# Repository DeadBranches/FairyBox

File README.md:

# FairyBox

### Software
A fork of [LilyTiny TinyTwinkle](https://github.com/deadbranch-forks/LilyTiny_LilyTwinkle)

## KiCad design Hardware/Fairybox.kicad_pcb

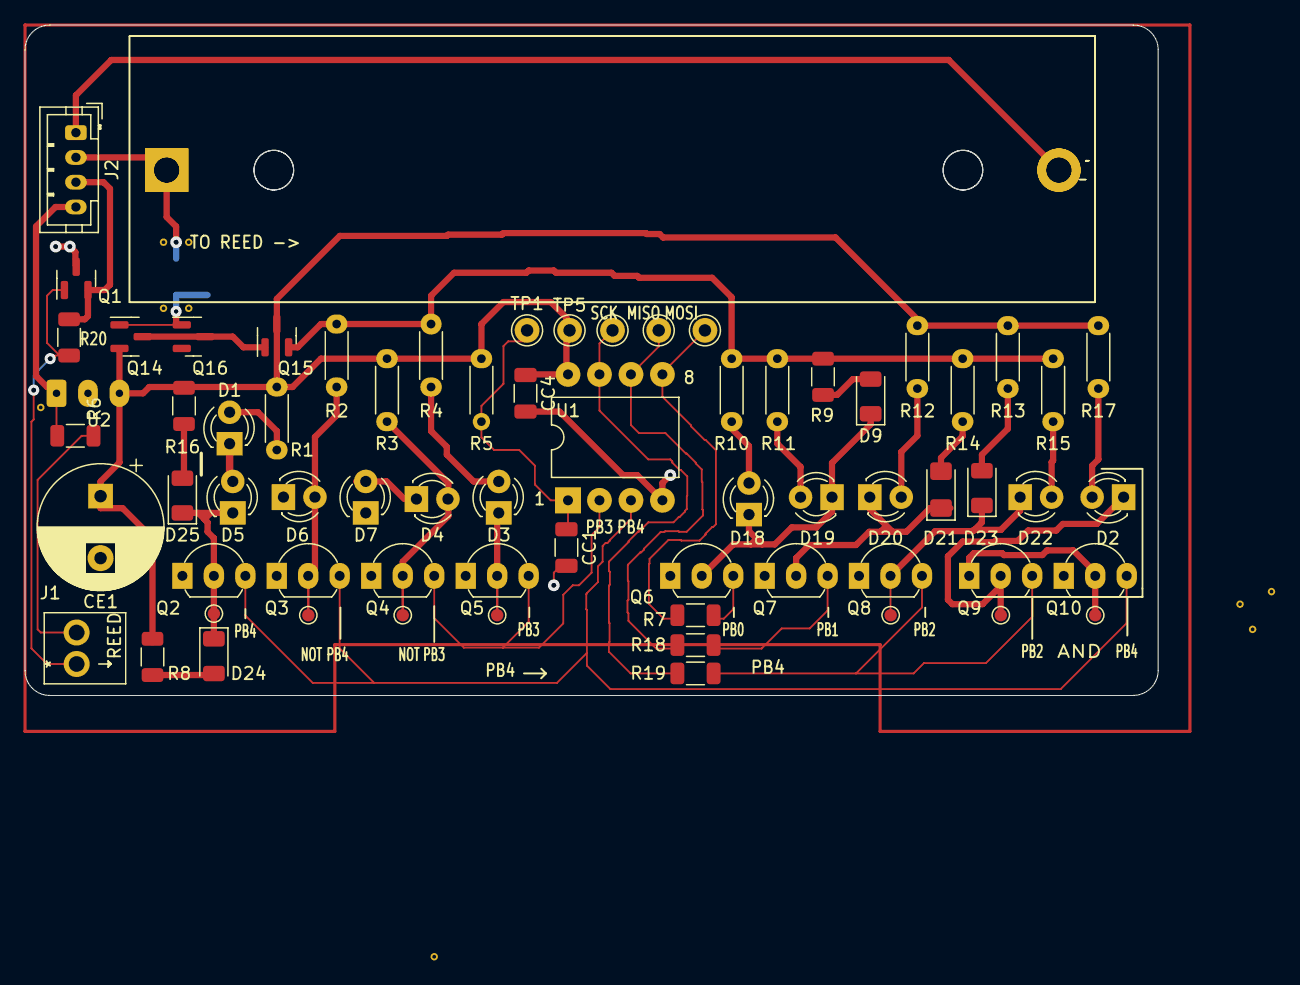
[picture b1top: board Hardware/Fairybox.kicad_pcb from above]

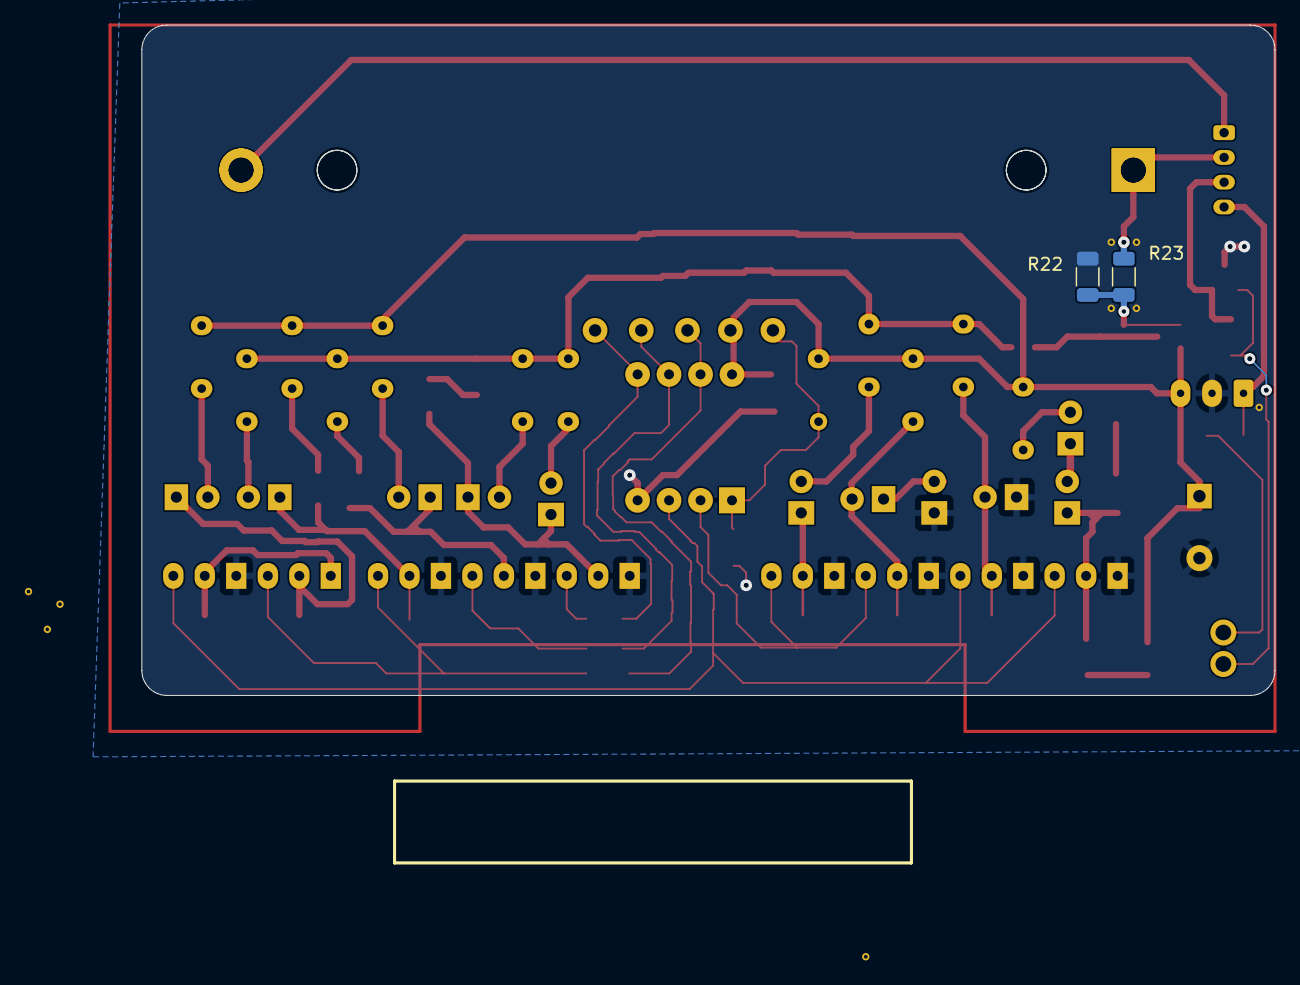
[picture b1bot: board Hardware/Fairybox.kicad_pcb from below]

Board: 2 copper layers, 91.4 x 54.1 mm, 81 parts (2 on the bottom side), 43 nets.

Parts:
BAT1, BAT1#2: locked; 18650 battery sled 1x
CC1: 0.22uF; C_1206_3216Metric
CC4: locked; C_1206_3216Metric
CE1: locked; CP_Radial_D10.0mm_P5.00mm
D1, D2, D3, D5, D6, D7, D18, D19, D20, D22: locked; LED_D3.0mm-DRC-larger-silk-footprint
D4: RED; LED_D3.0mm-DRC-larger-silk-footprint
D9, D24: BLUE; D_1206_3216Metric
D21: BLUE; D_1206_3216Metric_Pad1.42x1.75mm_HandSolder
D23, D25: RED; D_1206_3216Metric
J1: REED; KF128-2P
J2: JST B4B-PH-K-S; JST_PH_B4B-PH-K_1x04_P2.00mm_Vertical
JP1, JP3, JP5, JP9: ViaGND; Via-GND
JP2, JP4, JP6, JP7, JP8: ViaGND; PTH-Test_Point
Q1: locked; SOT-23
Q2, Q3, Q4, Q5, Q6, Q7, Q8, Q9, Q10: locked; TO-92L_Inline_Wide
Q14: AO3401A; SOT-23
Q15, Q16: SI2302; SOT-23
R1, R2, R3, R4, R5, R10, R11, R12, R13, R14, R15, R17: locked; R_Axial_DIN0204_L3.6mm_D1.6mm_P5.08mm_Horizontal
R6: 10K; R_1206_3216Metric
R7, R8, R18, R19: 470R; R_1206_3216Metric
R9: ??R; R_1206_3216Metric
R16: locked; R_1206_3216Metric
R20: 100K; R_1206_3216Metric
R22: 1M; R_1206_3216Metric
R23: 330k; R_1206_3216Metric
TP1: RST; Pin_D1.0mm_L10.0mm
TP2: locked; Pin_D1.0mm_L10.0mm
TP3: MISO; Pin_D1.0mm_L10.0mm
TP4: MOSI; Pin_D1.0mm_L10.0mm
TP5: VCC; Pin_D1.0mm_L10.0mm
TP6: TPP; TestPoint_Pad_D1.0mm
TP7: Q3_COL TP; TestPoint_Pad_D1.0mm
TP8: Q2_TP; TestPoint_Pad_D1.0mm
TP9: Q5_COL TP; TestPoint_Pad_D1.0mm
TP10: Q8_COL_TP; TestPoint_Pad_D1.0mm
TP11: Q9_COL_TP; TestPoint_Pad_D1.0mm
TP12: Q10_COL_TP; TestPoint_Pad_D1.0mm
U1: ATTINY85; DIP-8_W10.16mm
U2: locked; 3p-P2.54mm-big-pad-wire-holes

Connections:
+5V: CC4.1, CE1.1, Q14.2 (S), Q15.3 (D), R1.1, R3.1, R5.2, R8.1, R12.1, R13.1, R16.1, R17.1, TP5.1, U1.8 (VCC), U2.3 (VOUT)
/+5V B-LED: Q15.2 (S), R2.1, R4.1, R9.1, R10.1, R11.1, R14.1, R15.1
/CHARGE BOARD OUT B+: J2.4, R6.2, U2.1 (VIN)
/CHARGE BOARD OUT B-: J2.3, Q1.2 (S), R20.1
/D1_AN: D1.2 (A), R1.2
/D2_AN: D2.2 (A), R17.2
/D3_AN: D3.2 (A), R4.2
/D5_AN: D1.1 (K), D5.2 (A)
/D6_AN: D6.2 (A), Q3.2 (C), R2.2, TP7.1
/D7_AN: D4.1 (K), D7.2 (A)
/D9_AN: D9.2 (A), R9.2
/D18_AN: D18.2 (A), R10.2
/D19_AN: D19.2 (A), R11.2
/D20_AN: D20.2 (A), R12.2
/D21_AN: D22.2 (A), R15.2
/D22_AN: D21.2 (A), R14.2
/D23_AN: D23.2 (A), R13.2
/D24_AN: D24.2 (A), R8.2
/D25_AN: D25.2 (A), R16.2
/LBAT_NOT: Q14.1 (G), Q16.1 (G), R22.1, R23.2
/LI-ION_NEG: BAT1.2 (-), BAT1#2.2 (-), J2.2
/LI-ION_POS: BAT1.1 (+), BAT1#2.1 (+), J2.1, R22.2
/MCU GPIO0 MOSI: Q6.3 (B), R7.2
/MCU GPIO1 MISO: Q7.3 (B), R18.2
/MCU GPIO2 SCK: Q8.3 (B), Q9.3 (B), R19.2
/MCU GPIO3: Q4.3 (B), Q5.3 (B), U1.2 (PB3)
/MCU GPIO4: Q2.3 (B), Q3.3 (B), Q10.3 (B), U1.3 (PB4)
/MCU RST: CC1.1, R5.1, TP1.1, U1.1 (RST)
/PB0 PHY: R7.1, TP4.1, U1.5 (PB0)
/PB1 PHY: R18.1, TP3.1, U1.6 (PB1)
/PB2 PHY: R19.1, TP2.1, U1.7 (PB2)
/Q1_GATE: J1.2, Q1.1 (G), R20.2
/Q2_COL: D5.1 (K), D24.1 (K), D25.1 (K), Q2.2 (C), TP8.1
/Q4_COL: D4.2 (A), Q4.2 (C), R3.2, TP6.1
/Q5_COL: D3.1 (K), Q5.2 (C), TP9.1
/Q6_COL: D9.1 (K), D18.1 (K), D19.1 (K), Q6.2 (C)
/Q7_COL: D20.1 (K), D21.1 (K), Q7.2 (C)
/Q8_COL: D22.1 (K), D23.1 (K), Q8.2 (C), TP10.1
/Q9_COL: D2.1 (K), Q9.2 (C), TP11.1
/Q10_COL: Q9.1 (E), Q10.2 (C), TP12.1
/Q15_COL: Q14.3 (D), Q15.1 (G), Q16.3 (D)
/REED_IN: J1.1, R6.1
GND: CC1.2, CC4.2, CE1.2, D6.1 (K), D7.1 (K), JP1.1 (GND), JP2.1 (GND), JP3.1 (GND), JP4.1 (GND), JP5.1 (GND), JP6.1 (GND), JP7.1 (GND), JP8.1 (GND), JP9.1 (GND), Q1.3 (D), Q2.1 (E), Q3.1 (E), Q4.1 (E), Q5.1 (E), Q6.1 (E), Q7.1 (E), Q8.1 (E), Q10.1 (E), Q16.2 (S), R23.1, U2.2 (GND)

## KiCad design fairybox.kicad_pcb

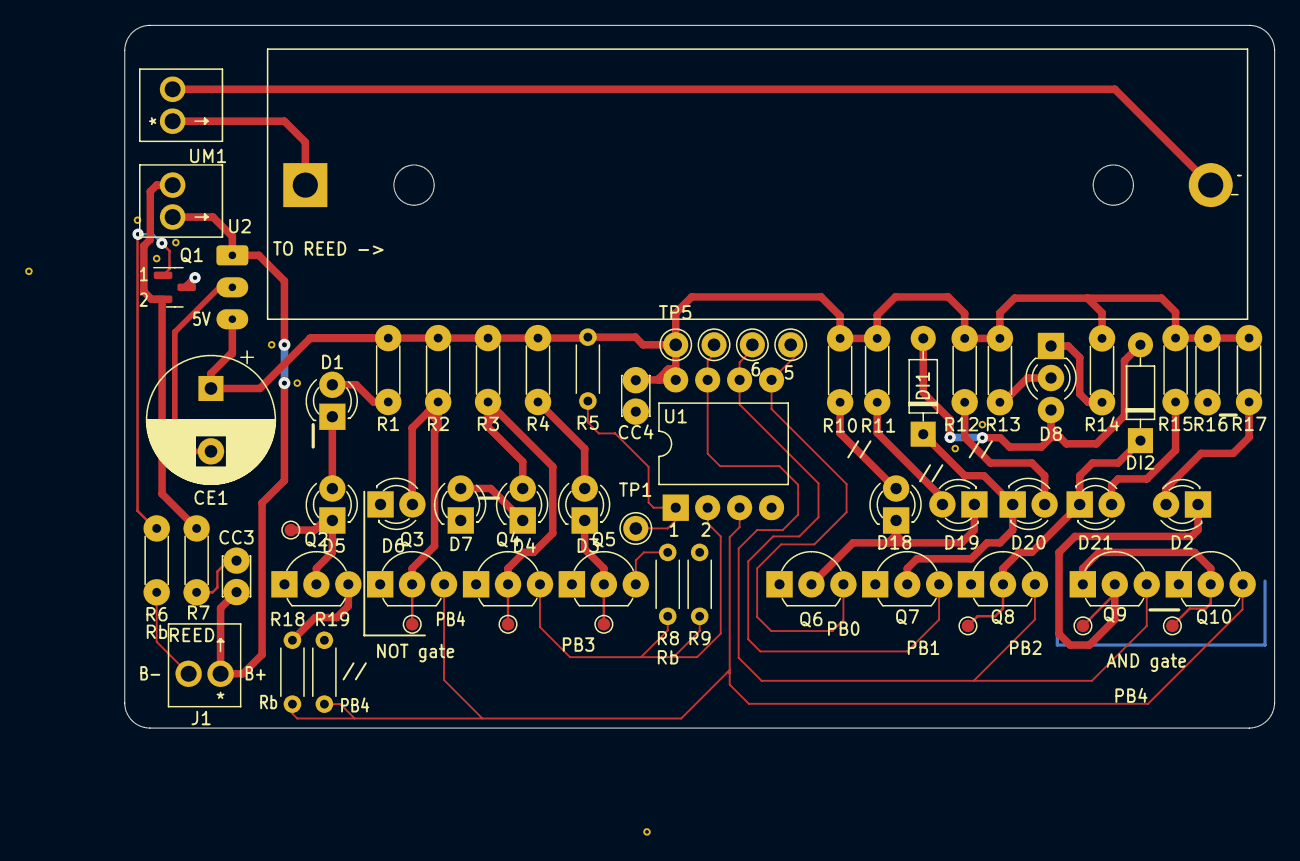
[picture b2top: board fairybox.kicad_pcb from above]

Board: 2 copper layers, 91.4 x 55.9 mm, 72 parts (0 on the bottom side), 38 nets.

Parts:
BAT1: locked; 18650 battery sled 1x
CC3, CC4: locked; C_Disc_D3.0mm_W2.0mm_P2.50mm
CE1: locked; CP_Radial_D10.0mm_P5.00mm
D1, D2, D3, D4, D5, D6, D7, D18, D19, D20, D21: locked; LED_D3.0mm-DRC-larger-silk-footprint
D8: locked; LED_D3.0mm-3
DI1: 1N914; D_DO-35_SOD27_P7.62mm_Horizontal
DI2: locked; D_DO-35_SOD27_P7.62mm_Horizontal
J1: REED; KF128-2P
JP1, JP2, JP3, JP4, JP5, JP6, JP7, JP8, JP9: ViaGND; Via-GND
Q1: locked; SOT-23
Q2, Q3, Q4, Q5, Q6, Q7, Q8, Q9, Q10: locked; TO-92L_Inline_Wide
R1, R2, R3, R4, R5, R6, R7, R10, R11, R12, R13, R14, R15, R16, R17, R18, R19: locked; R_Axial_DIN0204_L3.6mm_D1.6mm_P5.08mm_Horizontal
R8: 4.7K; R_Axial_DIN0204_L3.6mm_D1.6mm_P5.08mm_Horizontal
R9: 47K; R_Axial_DIN0204_L3.6mm_D1.6mm_P5.08mm_Horizontal
TP1, TP2, TP3, TP4, TP5: locked; Pin_D1.0mm_L10.0mm
TP6, TP7: TP; TestPoint_Pad_D1.0mm
TP8, TP10, TP11, TP12: TestPoint_Small; TestPoint_Pad_D1.0mm
TP9: tp; TestPoint_Pad_D1.0mm
U1: locked; DIP-8_W10.16mm
U2: locked; 3p-P2.54mm-big-pad-wire-holes
UM1: HW-107; HW-107 2.54mm terminals

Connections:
+5V: CC4.1, CE1.1, R1.1, R2.1, R3.1, R4.1, R5.2, R10.1, R11.1, R12.1, R13.1, R14.1, R15.1, R16.1, R17.1, TP5.1, U1.8 (VCC), U2.3 (VOUT)
+BATT: CC3.1, J1.1, U2.1 (VIN), UM1.3 (OUT+)
-BATT: Q1.2 (S), R7.1, UM1.4 (OUT-)
/B+: BAT1.1 (+), UM1.5 (B+)
/B-: BAT1.2 (-), UM1.6 (B-)
/D1_AN: D1.2 (A), R1.2
/D2_AN: D2.2 (A), R17.2
/D3_AN: D3.2 (A), R4.2
/D5_AN: D1.1 (K), D5.2 (A)
/D7_AN: D4.1 (K), D7.2 (A)
/D8_AN1: D8.1 (A1), R14.2
/D8_AN2: D8.2 (A2), R13.2
/D18_AN: D18.2 (A), R10.2
/D19_AN: D19.2 (A), R11.2
/D20_AN: D20.2 (A), R12.2
/D21_AN: D21.2 (A), R15.2
/MCU GPIO0 MOSI: Q6.3 (B), TP4.1, U1.5 (PB0)
/MCU GPIO1 MISO: Q7.3 (B), TP3.1, U1.6 (PB1)
/MCU GPIO2 SCK: Q8.3 (B), Q9.3 (B), TP2.1, U1.7 (PB2)
/MCU GPIO3: Q4.3 (B), R8.1, R9.1, U1.2 (PB3)
/MCU GPIO4: Q3.3 (B), Q10.3 (B), R18.1, R19.1, U1.3 (PB4)
/Q1_BASE: Q1.1 (G), R6.1
/Q2_BASE: Q2.3 (B), R18.2
/Q2_COL: D5.1 (K), Q2.2 (C), TP8.1
/Q3_COL: D6.2 (A), Q3.2 (C), R2.2, TP7.1
/Q4_COL: D4.2 (A), Q4.2 (C), R3.2, TP6.1
/Q5_BASE: Q5.3 (B), R8.2
/Q5_COL: D3.1 (K), Q5.2 (C), TP9.1
/Q6_COL: D18.1 (K), D19.1 (K), Q6.2 (C)
/Q7_COL: D20.1 (K), DI1.1 (K), Q7.2 (C)
/Q8_COL: D21.1 (K), DI2.1 (K), Q8.2 (C), TP10.1
/Q9_COL: D2.1 (K), Q9.2 (C), TP11.1
/Q10_COL: Q9.1 (E), Q10.2 (C), TP12.1
/REED_RETURN: J1.2, R6.2
/RP8: CC3.2, R7.2
/SPI RST: R5.1, TP1.1, U1.1 (RST)
GND: CC4.2, CE1.2, D6.1 (K), D7.1 (K), JP1.1 (GND), JP2.1 (GND), JP3.1 (GND), JP4.1 (GND), JP5.1 (GND), JP6.1 (GND), JP7.1 (GND), JP8.1 (GND), JP9.1 (GND), Q1.3 (D), Q2.1 (E), Q3.1 (E), Q4.1 (E), Q5.1 (E), Q6.1 (E), Q7.1 (E), Q8.1 (E), Q10.1 (E), R9.2, R19.2, U1.4 (GND), U2.2 (GND)
unnamed: D8.3 (K), DI1.2 (A), DI2.2 (A)

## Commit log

2022-10-16 GPIO Assignment Changes
    In order to enable more efficient signal trace routing transistor base pins were reassigned to different MCU signal pins. The new order no longer has signal traces crossing paths to get to their dest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
    This routing is much simpler and improves the chances of a successful (functioning) PCB.
    - Easier to manufacture. Not pushing JLCPCB's manufacturing capabilities is a good thing.
    - Likely less unintended EMI radiation.
    - Less opportunities for signal crosstalk.
2022-10-16 MCU reset pin and resistor fix
    Attiny85 Reset Pin
    - Rotated pull-up resistor R5. 5V pad now faces north.
    - Extended 5V copper pour to include R5
2022-10-16 Eliminating Q10_COL via
    Re-routed Q9_COL around Q9 to eliminate the need for the Q10_COL net via.
2022-10-16 Removed bulk capacitor power puddle
    Replaced CE1<>U2 copper pour with a 0.600mm track.
2022-10-17 Updated solder mask labels
    Moved component reference designators around. Added some informational text to the solder mask
2022-10-19 Cleanup
    alignment and other misc changes.
2022-10-19 Squashed 'Software/' content from commit e6529b9
    git-subtree-dir: Software
    git-subtree-split: e6529b98b5d86a572c899e30b436f2d592f5a127
2022-10-19 Rename LilyTwinkle.ino to FairyBox.ino
2022-10-19 Moving Fairybox.ino to repository root
2022-10-19 Directory restructure
2022-10-19 Adding kicad project files
2022-10-19 Testing kicad/github interoperability
2022-10-19 Testing kicad/github interoperability v2
2022-10-20 Testing how symlinks interact with git. FairyBoxTest.ino is a symlink to the ArduinoIDE sketch folder elsewhere on the drive.
2022-10-20 testing symlinks. Updated /f/c/code - arduino sketchbooks/fairybox - branch_main/fairybox - branch_main.ino with a comment. Seeing if giit picks it up.
2022-10-20 Update FairyBoxTest.ino
    // Test. #2. Modified file on remote repo to see what happens when
    // a remotely modified file it is pulled to the local repo when the local
    // file is a symlink to another directory.
2022-10-21 Testing git and ArduinoIDE links. File in arduino sketch folder is a symlink to local git repo. With ArduinoIDE, opened sketch, made a change, saved. Git picked up the change. Pushing it to remote re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
2022-10-21 test
2022-10-21 Misc changes I forget
2022-10-21 Removing relocated kicad project files.
2022-10-24 Misc hardware changes
2022-10-24 Update Fairybox.kicad_pro
    Sync with local
2022-10-24 Update Fairybox.kicad_sch
    Sync with local
2022-10-24 Delete Software directory
    Removing software directory to simplify project. Software files remain at
    https://github.com/deadbranch-forks/LilyTiny_LilyTwinkle
2022-10-25 Updated testpoints and silkscreen
2022-10-26 misc
2022-10-27 PCB layout tweaks
2022-10-27 added attiny84 footprint
2022-10-28 I forget
2022-10-28 Power Delivery EEschema - Added two 1x2P 2.5mm pitch pin header symbols with associated footprints to replace the custom liion charge breakout board symbol/footprints - Moved liion charge board and n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
    MCU
    EEschema
    - Added 220R series resistors (R7, R18, R19) to each MCU pin used for SPI in circuit programming. Protects the programmer GPIO pins from voltages greater than 22mA
    PCBnew
    - 220R series resistors added to SPI lines at the bottom of the board. Sh
2022-10-31 JST connector, Rule Zone Added JST PH connector instead of screw terminals. Corrected keepout zone.
2022-10-31 Rolling back some changes.
2022-11-11 many
2022-11-12 a lot
2022-11-13 Edge cut.
2022-11-30 not sure
